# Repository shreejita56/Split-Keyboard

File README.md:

# Split-Keyboard

SO I made a custom 60 % layout  Split Mechanical keyboard which has a rotor encoder at the top for brightness controlee as well . It is based on Xiao rp2040 . As it has very few pins So I had to use 2 Expanders one for each Split . The communication between 2 Splits happens with the USB-C to USB-C Connection. And We hade intricated per switch LEDs as  well . The Split Keyboard have magnets by the side SO that we could join the split and make it a big single keyboard if we want or use it as a split.  The PCB was designed on kicad and CAD was done on Fusion . firmware was written in VS-Code. It has a very compact design. The Keyboard also includes per switch LED and diodes to prevent ghosting. 

## Features

 - Based on Xiao Rp2040
 - It has A split Keyboard Design
 - had compact 60% keyboard layout
 - Per Switch LED and diode for ghosting prevention
 - Uplifted CAD Design for comfortable typing
 - Has magnets at the Edges So that the Split could be connected and used as a Simple Keyboard
   
## BOM

| Item | Price (USD) | Source |
|---|---:|---|
| PCB + Shipping + 3D Prints - Coupons | $23.14 | https://jlcpcb.com/|
| KeyCaps | $15.04 | https://meckeys.com/shop/accessories/keyboard-accessories/keycaps/ranuw-keycap-set/ |
| Stabilizers | $10.76 | https://meckeys.com/shop/accessories/keyboard-accessories/more/glorious-goat-stabilizers/ |
| Switches (Pack of 10) × 7 | $22.10 | https://meckeys.com/shop/accessories/keyboard-accessories/key-switches/hmx-xinhai-switch/?attribute_pa_key-switches=hmx-xinhai-45g|
| PCA9555 Expander × 2 | $6.22 | https://robu.in/product/pca9555dwr-texas-instruments-400khz-soic-24-300mil-i-o-expanders-rohs/ |
| Seeed Studio XIAO RP2040 | $5.92 | https://robu.in/product/seeed-studio-xiao-rp2040-v1-0/ |
| 1N4148W-T4 Diodes (Pack of 15) × 70 | $3.20 | https://sharvielectronics.com/product/a7-1n4007-100v-1a-silicon-rectifier-diode-sod-123fl-smd-package/|
| SK6812MINI-E | $8.10 | https://www.etstore.in/products/e9974?variant=48993209319675|
| Components Shipping | $3.30 |https://sharvielectronics.com/ / https://meckeys.com / https://robu.in |
| **Total** | **$97.78** | |

### Schematic<br><br>

###  PCB Design<br><br>

### 3D Render <br><br>

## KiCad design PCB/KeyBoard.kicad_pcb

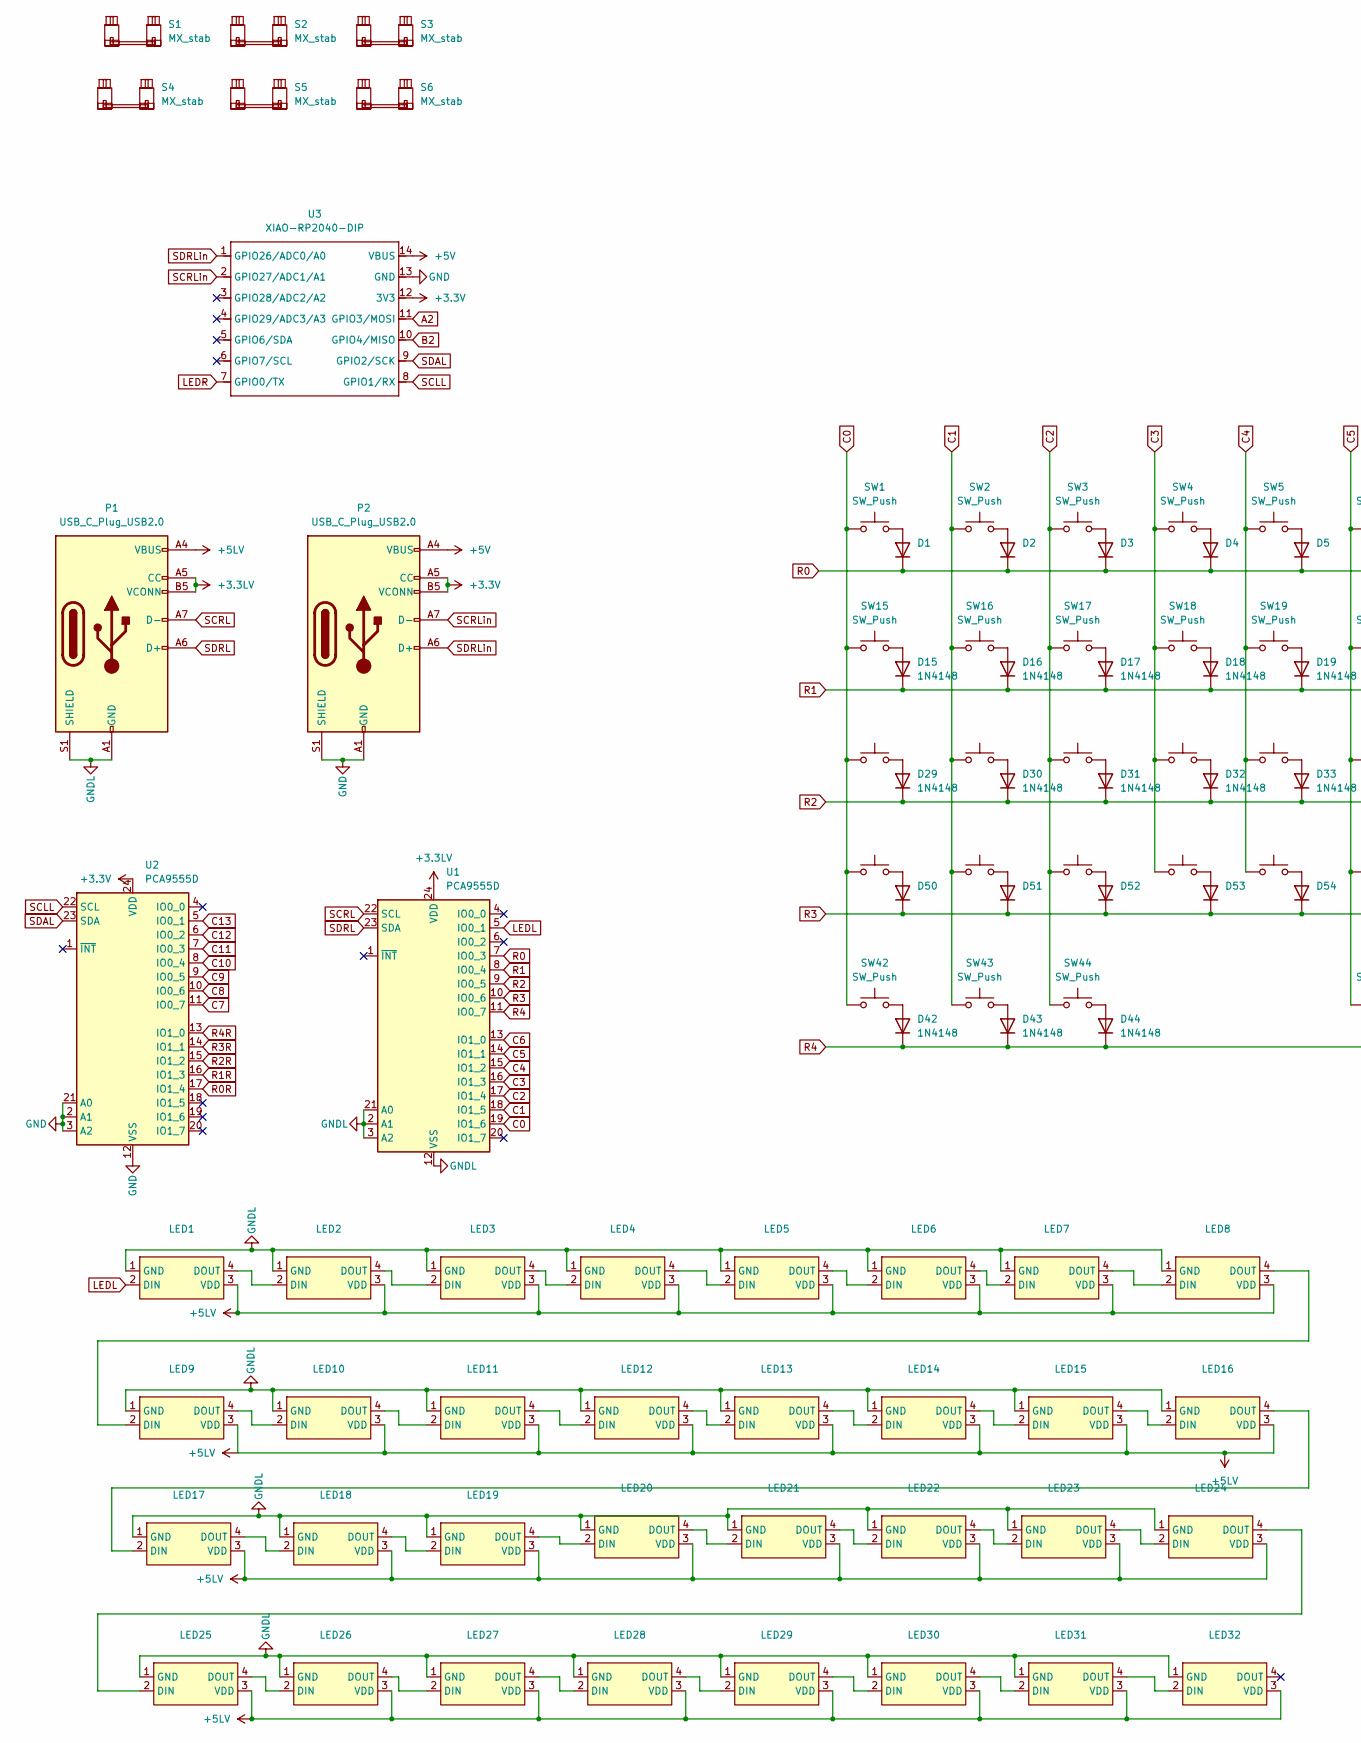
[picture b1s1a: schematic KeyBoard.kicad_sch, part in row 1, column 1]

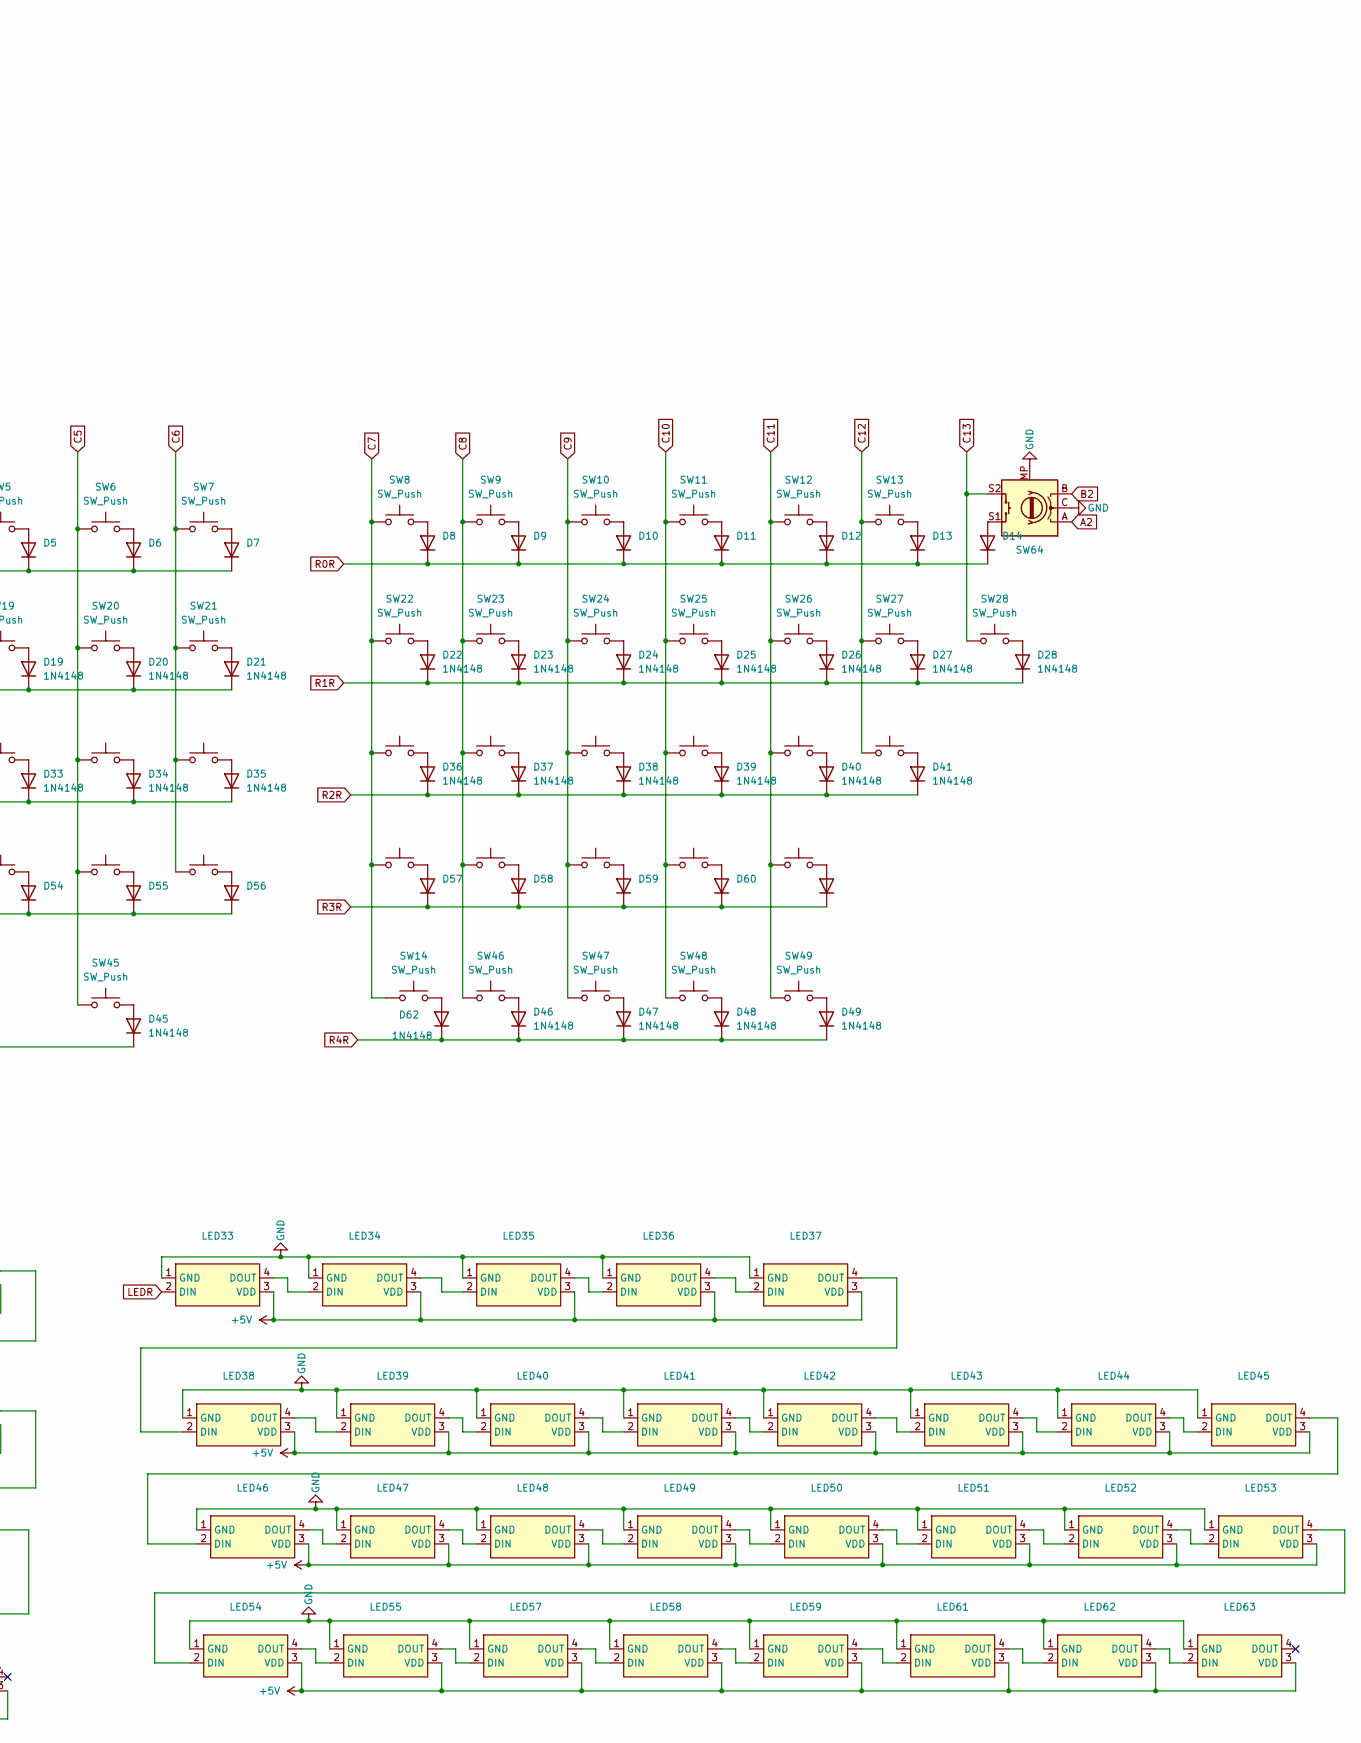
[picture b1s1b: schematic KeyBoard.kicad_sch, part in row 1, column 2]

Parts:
D1, D2, D3, D4, D5, D6, D7, D8, D9, D10, D11, D12, D13, D14, D15, D16, D17, D18, D19, D20, D21, D22, D23, D24, D25, D26, D27, D28, D29, D30, D31, D32, D33, D34, D35, D36, D37, D38, D39, D40, D41, D42, D43, D44, D45, D46, D47, D48, D49, D50, D51, D52, D53, D54, D55, D56, D57, D58, D59, D60, D61, D62: 1N4148; D_DO-35_SOD27_P7.62mm_Horizontal
LED1, LED2, LED3, LED4, LED5, LED6, LED7, LED8, LED9, LED10, LED11, LED12, LED13, LED14, LED15, LED16, LED17, LED18, LED19, LED20, LED21, LED22, LED23, LED24, LED25, LED26, LED27, LED28, LED29, LED30, LED31, LED32, LED33, LED34, LED35, LED36, LED37, LED38, LED39, LED40, LED41, LED42, LED43, LED44, LED45, LED46, LED47, LED48, LED49, LED50, LED51, LED52, LED53, LED54, LED55, LED57, LED58, LED59, LED61, LED62, LED63: SK6812MINI-E_C5149201; LED-SMD_4P-L3.2-W2.8-LS5.9_SK6812MINI-E; MPN SK6812MINI-E; LCSC Part C5149201
P1, P2: USB_C_Plug_USB2.0; USB_C_Receptacle_HRO_TYPE-C-31-M-12
S1: MX_stab; STAB_MX_2u
S2, S3: MX_stab; STAB_MX_2.25u
S4, S5, S6: MX_stab; STAB_MX_2.75u
SW1, SW2, SW3, SW4, SW5, SW6, SW7, SW8, SW9, SW10, SW11, SW12, SW13, SW16, SW17, SW18, SW19, SW20, SW21, SW22, SW23, SW24, SW25, SW26, SW27, SW30, SW31, SW32, SW33, SW34, SW35, SW36, SW37, SW38, SW39, SW40, SW51, SW52, SW53, SW54, SW55, SW56, SW57, SW58, SW59, SW60: SW_Push; SW_Cherry_MX_1.00u_PCB
SW14, SW45, SW61: SW_Push; SW_Cherry_MX_2.75u_PCB
SW15: SW_Push; SW_Cherry_MX_1.50u_PCB
SW28: SW_Push; SW_Cherry_MX_1.50u_Plate
SW29: SW_Push; SW_Cherry_MX_1.75u_PCB
SW41, SW50: SW_Push; SW_Cherry_MX_2.25u_PCB
SW42, SW43, SW44, SW46, SW48, SW49: SW_Push; SW_Cherry_MX_1.25u_PCB
SW47: SW_Push; SW_Cherry_MX_1.25u_Plate
SW64: RotaryEncoder_Switch_MP; RotaryEncoder_Alps_EC11E-Switch_Vertical_H20mm
U1, U2: PCA9555D; SOIC-24W_7.5x15.4mm_P1.27mm
U3: XIAO-RP2040-DIP; XIAO-RP2040-SMD

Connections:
+3.3LV: P1.A5 (CC), P1.B5 (VCONN), U1.24 (VDD)
+3.3V: P2.A5 (CC), P2.B5 (VCONN), U2.24 (VDD), U3.12 (3V3)
+5LV: LED1.3 (VDD), LED2.3 (VDD), LED3.3 (VDD), LED4.3 (VDD), LED5.3 (VDD), LED6.3 (VDD), LED7.3 (VDD), LED8.3 (VDD), LED9.3 (VDD), LED10.3 (VDD), LED11.3 (VDD), LED12.3 (VDD), LED13.3 (VDD), LED14.3 (VDD), LED15.3 (VDD), LED16.3 (VDD), LED17.3 (VDD), LED18.3 (VDD), LED19.3 (VDD), LED20.3 (VDD), LED21.3 (VDD), LED22.3 (VDD), LED23.3 (VDD), LED24.3 (VDD), LED25.3 (VDD), LED26.3 (VDD), LED27.3 (VDD), LED28.3 (VDD), LED29.3 (VDD), LED30.3 (VDD), LED31.3 (VDD), LED32.3 (VDD), P1.A4 (VBUS), P1.A9 (VBUS), P1.B4 (VBUS), P1.B9 (VBUS)
+5V: LED33.3 (VDD), LED34.3 (VDD), LED35.3 (VDD), LED36.3 (VDD), LED37.3 (VDD), LED38.3 (VDD), LED39.3 (VDD), LED40.3 (VDD), LED41.3 (VDD), LED42.3 (VDD), LED43.3 (VDD), LED44.3 (VDD), LED45.3 (VDD), LED46.3 (VDD), LED47.3 (VDD), LED48.3 (VDD), LED49.3 (VDD), LED50.3 (VDD), LED51.3 (VDD), LED52.3 (VDD), LED53.3 (VDD), LED54.3 (VDD), LED55.3 (VDD), LED57.3 (VDD), LED58.3 (VDD), LED59.3 (VDD), LED61.3 (VDD), LED62.3 (VDD), LED63.3 (VDD), P2.A4 (VBUS), P2.A9 (VBUS), P2.B4 (VBUS), P2.B9 (VBUS), U3.14 (VBUS)
A2: SW64.A, U3.11 (GPIO3/MOSI)
B2: SW64.B, U3.10 (GPIO4/MISO)
C0: SW1.1, SW15.1, SW29.1, SW42.1, SW50.1, U1.19 (IO1_6)
C1: SW2.1, SW16.1, SW30.1, SW43.1, SW51.1, U1.18 (IO1_5)
C2: SW3.1, SW17.1, SW31.1, SW44.1, SW52.1, U1.17 (IO1_4)
C3: SW4.1, SW18.1, SW32.1, SW53.1, U1.16 (IO1_3)
C4: SW5.1, SW19.1, SW33.1, SW54.1, U1.15 (IO1_2)
C5: SW6.1, SW20.1, SW34.1, SW45.1, SW55.1, U1.14 (IO1_1)
C6: SW7.1, SW21.1, SW35.1, SW56.1, U1.13 (IO1_0)
C7: SW8.1, SW14.1, SW22.1, SW36.1, SW57.1, U2.11 (IO0_7)
C8: SW9.1, SW23.1, SW37.1, SW46.1, SW58.1, U2.10 (IO0_6)
C9: SW10.1, SW24.1, SW38.1, SW47.1, SW59.1, U2.9 (IO0_5)
C10: SW11.1, SW25.1, SW39.1, SW48.1, SW60.1, U2.8 (IO0_4)
C11: SW12.1, SW26.1, SW40.1, SW49.1, SW61.1, U2.7 (IO0_3)
C12: SW13.1, SW27.1, SW41.1, U2.6 (IO0_2)
C13: SW28.1, SW64.S2, U2.5 (IO0_1)
GND: LED33.1 (GND), LED34.1 (GND), LED35.1 (GND), LED36.1 (GND), LED37.1 (GND), LED38.1 (GND), LED39.1 (GND), LED40.1 (GND), LED41.1 (GND), LED42.1 (GND), LED43.1 (GND), LED44.1 (GND), LED45.1 (GND), LED46.1 (GND), LED47.1 (GND), LED48.1 (GND), LED49.1 (GND), LED50.1 (GND), LED51.1 (GND), LED52.1 (GND), LED53.1 (GND), LED54.1 (GND), LED55.1 (GND), LED57.1 (GND), LED58.1 (GND), LED59.1 (GND), LED61.1 (GND), LED62.1 (GND), LED63.1 (GND), P2.A1 (GND), P2.A12 (GND), P2.B1 (GND), P2.B12 (GND), P2.S1 (SHIELD), SW64.C, SW64.MP, U2.2 (A1), U2.3 (A2), U2.12 (VSS), U2.21 (A0), U3.13 (GND)
GNDL: LED1.1 (GND), LED2.1 (GND), LED3.1 (GND), LED4.1 (GND), LED5.1 (GND), LED6.1 (GND), LED7.1 (GND), LED8.1 (GND), LED9.1 (GND), LED10.1 (GND), LED11.1 (GND), LED12.1 (GND), LED13.1 (GND), LED14.1 (GND), LED15.1 (GND), LED16.1 (GND), LED17.1 (GND), LED18.1 (GND), LED19.1 (GND), LED20.1 (GND), LED21.1 (GND), LED22.1 (GND), LED23.1 (GND), LED24.1 (GND), LED25.1 (GND), LED26.1 (GND), LED27.1 (GND), LED28.1 (GND), LED29.1 (GND), LED30.1 (GND), LED31.1 (GND), LED32.1 (GND), P1.A1 (GND), P1.A12 (GND), P1.B1 (GND), P1.B12 (GND), P1.S1 (SHIELD), U1.2 (A1), U1.3 (A2), U1.12 (VSS), U1.21 (A0)
LEDL: LED1.2 (DIN), U1.5 (IO0_1)
LEDR: LED33.2 (DIN), U3.7 (GPIO0/TX)
unnamed: D1.2 (A), SW1.2
unnamed: D2.2 (A), SW2.2
unnamed: D3.2 (A), SW3.2
unnamed: D4.2 (A), SW4.2
unnamed: D5.2 (A), SW5.2
unnamed: D6.2 (A), SW6.2
unnamed: D7.2 (A), SW7.2
unnamed: D8.2 (A), SW8.2
unnamed: D9.2 (A), SW9.2
unnamed: D10.2 (A), SW10.2
unnamed: D11.2 (A), SW11.2
unnamed: D12.2 (A), SW12.2
unnamed: D13.2 (A), SW13.2
unnamed: D14.2 (A), SW64.S1
unnamed: D15.2 (A), SW15.2
unnamed: D16.2 (A), SW16.2
unnamed: D17.2 (A), SW17.2
unnamed: D18.2 (A), SW18.2
unnamed: D19.2 (A), SW19.2
unnamed: D20.2 (A), SW20.2
unnamed: D21.2 (A), SW21.2
unnamed: D22.2 (A), SW22.2
unnamed: D23.2 (A), SW23.2
unnamed: D24.2 (A), SW24.2
unnamed: D25.2 (A), SW25.2
unnamed: D26.2 (A), SW26.2
unnamed: D27.2 (A), SW27.2
unnamed: D28.2 (A), SW28.2
unnamed: D29.2 (A), SW29.2
unnamed: D30.2 (A), SW30.2
unnamed: D31.2 (A), SW31.2
unnamed: D32.2 (A), SW32.2
unnamed: D33.2 (A), SW33.2
unnamed: D34.2 (A), SW34.2
unnamed: D35.2 (A), SW35.2
unnamed: D36.2 (A), SW36.2
unnamed: D37.2 (A), SW37.2
unnamed: D38.2 (A), SW38.2
unnamed: D39.2 (A), SW39.2
unnamed: D40.2 (A), SW40.2
unnamed: D41.2 (A), SW41.2
unnamed: D42.2 (A), SW42.2
unnamed: D43.2 (A), SW43.2
unnamed: D44.2 (A), SW44.2
unnamed: D45.2 (A), SW45.2
unnamed: D46.2 (A), SW46.2
unnamed: D47.2 (A), SW47.2
unnamed: D48.2 (A), SW48.2
unnamed: D49.2 (A), SW49.2
unnamed: D50.2 (A), SW50.2
unnamed: D51.2 (A), SW51.2
unnamed: D52.2 (A), SW52.2
unnamed: D53.2 (A), SW53.2
unnamed: D54.2 (A), SW54.2
unnamed: D55.2 (A), SW55.2
unnamed: D56.2 (A), SW56.2
unnamed: D57.2 (A), SW57.2
unnamed: D58.2 (A), SW58.2
unnamed: D59.2 (A), SW59.2
unnamed: D60.2 (A), SW60.2
unnamed: D61.2 (A), SW61.2
unnamed: D62.2 (A), SW14.2
unnamed: LED1.4 (DOUT), LED2.2 (DIN)
unnamed: LED2.4 (DOUT), LED3.2 (DIN)
unnamed: LED3.4 (DOUT), LED4.2 (DIN)
unnamed: LED4.4 (DOUT), LED5.2 (DIN)
unnamed: LED5.4 (DOUT), LED6.2 (DIN)
unnamed: LED6.4 (DOUT), LED7.2 (DIN)
unnamed: LED7.4 (DOUT), LED8.2 (DIN)
unnamed: LED8.4 (DOUT), LED9.2 (DIN)
unnamed: LED9.4 (DOUT), LED10.2 (DIN)
unnamed: LED10.4 (DOUT), LED11.2 (DIN)
unnamed: LED11.4 (DOUT), LED12.2 (DIN)
unnamed: LED12.4 (DOUT), LED13.2 (DIN)
unnamed: LED13.4 (DOUT), LED14.2 (DIN)
unnamed: LED14.4 (DOUT), LED15.2 (DIN)
unnamed: LED15.4 (DOUT), LED16.2 (DIN)
unnamed: LED16.4 (DOUT), LED17.2 (DIN)
unnamed: LED17.4 (DOUT), LED18.2 (DIN)
unnamed: LED18.4 (DOUT), LED19.2 (DIN)
unnamed: LED19.4 (DOUT), LED20.2 (DIN)
unnamed: LED20.4 (DOUT), LED21.2 (DIN)
unnamed: LED21.4 (DOUT), LED22.2 (DIN)
unnamed: LED22.4 (DOUT), LED23.2 (DIN)
unnamed: LED23.4 (DOUT), LED24.2 (DIN)
unnamed: LED24.4 (DOUT), LED25.2 (DIN)
unnamed: LED25.4 (DOUT), LED26.2 (DIN)
unnamed: LED26.4 (DOUT), LED27.2 (DIN)
unnamed: LED27.4 (DOUT), LED28.2 (DIN)
unnamed: LED28.4 (DOUT), LED29.2 (DIN)
unnamed: LED29.4 (DOUT), LED30.2 (DIN)
unnamed: LED30.4 (DOUT), LED31.2 (DIN)
unnamed: LED31.4 (DOUT), LED32.2 (DIN)
unnamed: LED33.4 (DOUT), LED34.2 (DIN)
unnamed: LED34.4 (DOUT), LED35.2 (DIN)
unnamed: LED35.4 (DOUT), LED36.2 (DIN)
unnamed: LED36.4 (DOUT), LED37.2 (DIN)
unnamed: LED37.4 (DOUT), LED38.2 (DIN)
unnamed: LED38.4 (DOUT), LED39.2 (DIN)
unnamed: LED39.4 (DOUT), LED40.2 (DIN)
unnamed: LED40.4 (DOUT), LED41.2 (DIN)
unnamed: LED41.4 (DOUT), LED42.2 (DIN)
unnamed: LED42.4 (DOUT), LED43.2 (DIN)
unnamed: LED43.4 (DOUT), LED44.2 (DIN)
unnamed: LED44.4 (DOUT), LED45.2 (DIN)
unnamed: LED45.4 (DOUT), LED46.2 (DIN)
unnamed: LED46.4 (DOUT), LED47.2 (DIN)
unnamed: LED47.4 (DOUT), LED48.2 (DIN)
unnamed: LED48.4 (DOUT), LED49.2 (DIN)
unnamed: LED49.4 (DOUT), LED50.2 (DIN)
unnamed: LED50.4 (DOUT), LED51.2 (DIN)
unnamed: LED51.4 (DOUT), LED52.2 (DIN)
unnamed: LED52.4 (DOUT), LED53.2 (DIN)
unnamed: LED53.4 (DOUT), LED54.2 (DIN)
unnamed: LED54.4 (DOUT), LED55.2 (DIN)
unnamed: LED55.4 (DOUT), LED57.2 (DIN)
unnamed: LED57.4 (DOUT), LED58.2 (DIN)
unnamed: LED58.4 (DOUT), LED59.2 (DIN)
unnamed: LED59.4 (DOUT), LED61.2 (DIN)
unnamed: LED61.4 (DOUT), LED62.2 (DIN)
unnamed: LED62.4 (DOUT), LED63.2 (DIN)
R0: D1.1 (K), D2.1 (K), D3.1 (K), D4.1 (K), D5.1 (K), D6.1 (K), D7.1 (K), U1.7 (IO0_3)
R0R: D8.1 (K), D9.1 (K), D10.1 (K), D11.1 (K), D12.1 (K), D13.1 (K), D14.1 (K), U2.17 (IO1_4)
R1: D15.1 (K), D16.1 (K), D17.1 (K), D18.1 (K), D19.1 (K), D20.1 (K), D21.1 (K), U1.8 (IO0_4)
R1R: D22.1 (K), D23.1 (K), D24.1 (K), D25.1 (K), D26.1 (K), D27.1 (K), D28.1 (K), U2.16 (IO1_3)
R2: D29.1 (K), D30.1 (K), D31.1 (K), D32.1 (K), D33.1 (K), D34.1 (K), D35.1 (K), U1.9 (IO0_5)
R2R: D36.1 (K), D37.1 (K), D38.1 (K), D39.1 (K), D40.1 (K), D41.1 (K), U2.15 (IO1_2)
R3: D50.1 (K), D51.1 (K), D52.1 (K), D53.1 (K), D54.1 (K), D55.1 (K), D56.1 (K), U1.10 (IO0_6)
R3R: D57.1 (K), D58.1 (K), D59.1 (K), D60.1 (K), D61.1 (K), U2.14 (IO1_1)
R4: D42.1 (K), D43.1 (K), D44.1 (K), D45.1 (K), U1.11 (IO0_7)
R4R: D46.1 (K), D47.1 (K), D48.1 (K), D49.1 (K), D62.1 (K), U2.13 (IO1_0)
SCLL: U2.22 (SCL), U3.8 (GPIO1/RX)
SCRL: P1.A7 (D-), U1.22 (SCL)
SCRLin: P2.A7 (D-), U3.2 (GPIO27/ADC1/A1)
SDAL: U2.23 (SDA), U3.9 (GPIO2/SCK)
SDRL: P1.A6 (D+), U1.23 (SDA)
SDRLin: P2.A6 (D+), U3.1 (GPIO26/ADC0/A0)

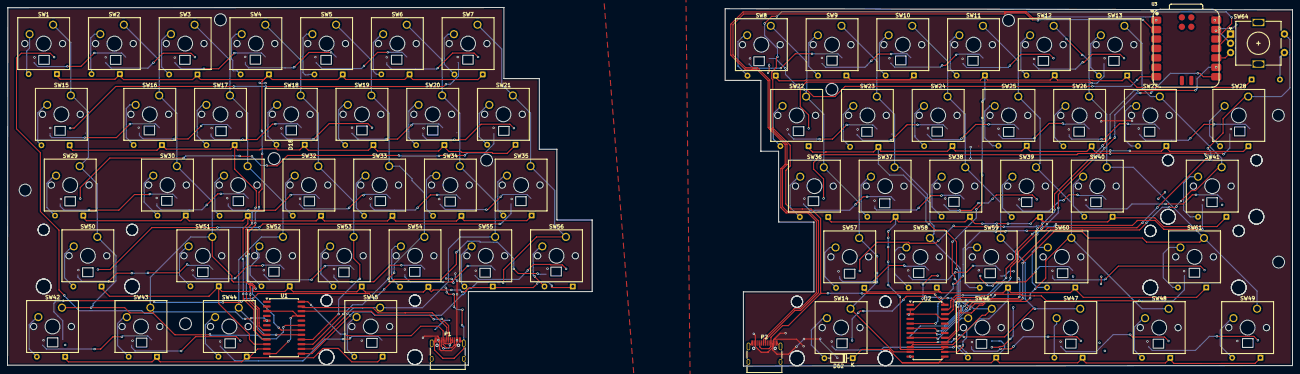
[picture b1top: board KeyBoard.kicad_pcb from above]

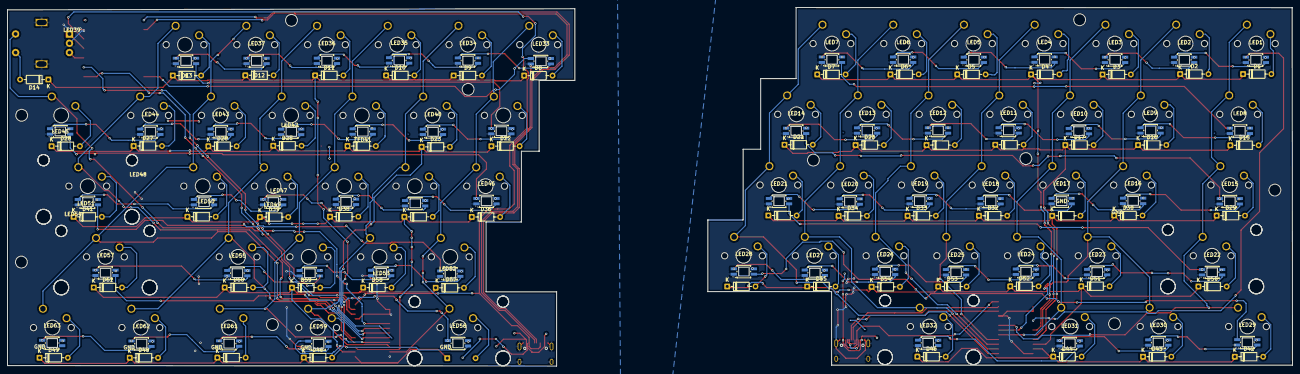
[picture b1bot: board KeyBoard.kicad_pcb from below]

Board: 2 copper layers, 346.1 x 96.6 mm, 195 parts (122 on the bottom side), 161 nets.
